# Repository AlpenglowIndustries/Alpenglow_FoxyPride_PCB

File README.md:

# Foxy_Pride_PCB
An awesome SMT soldering board with space for writing pronouns, where you can choose your own pride-themed colors for the LEDs.
The circuit uses a 555 timer to create a clock signal, which is fed into the decade counter to light the LEDs.
You can change the blink rate by swapping out the capacitor!

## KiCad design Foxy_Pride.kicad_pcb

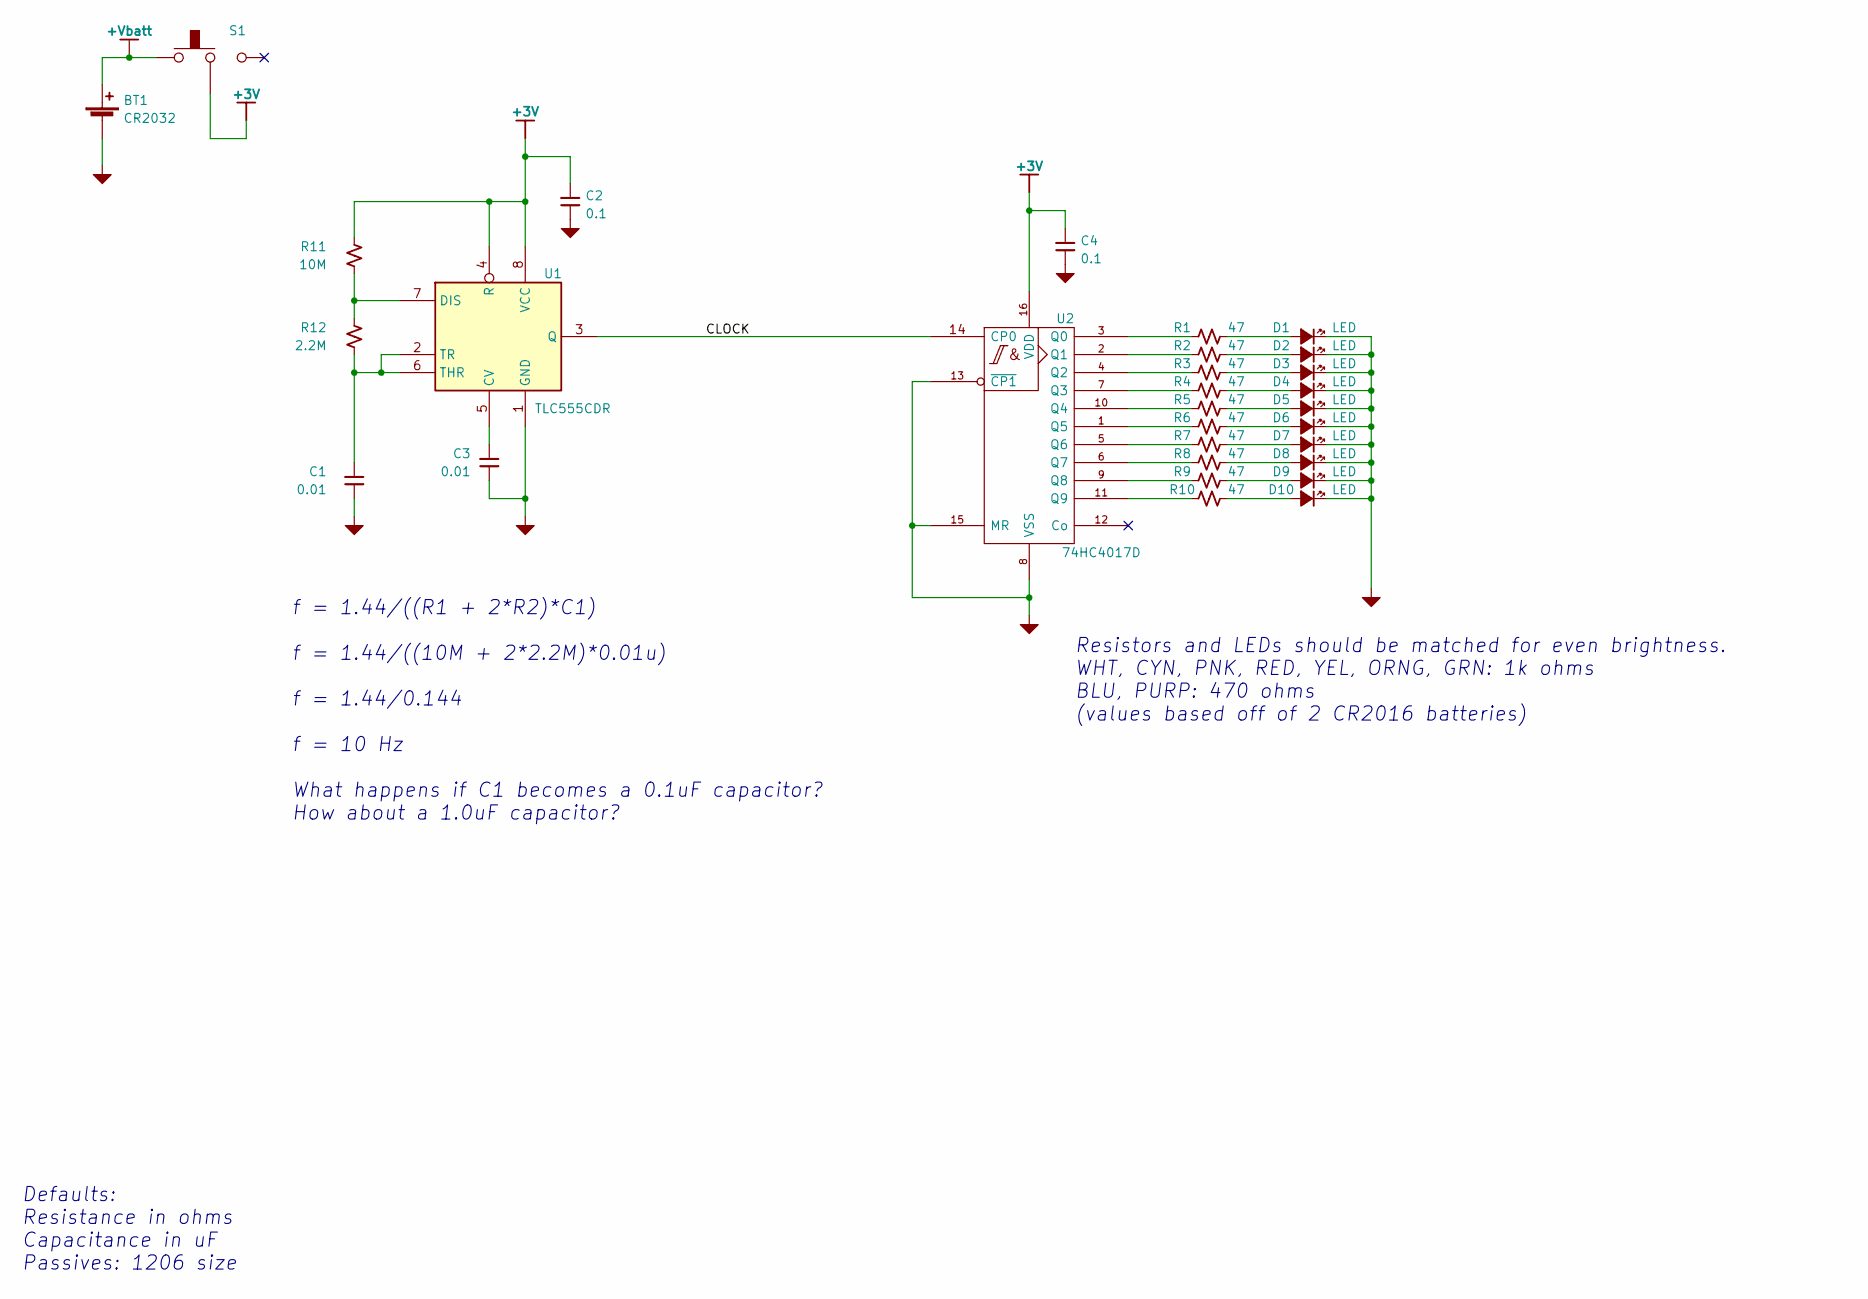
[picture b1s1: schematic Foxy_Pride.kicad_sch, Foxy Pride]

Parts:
BT1: CR2032; BatteryHolder_CR2032_SMT
C1, C3: 0.01; R_1206_3216Metric_Pad1.30x1.75mm_HandSolder
C2, C4: 0.1; R_1206_3216Metric_Pad1.30x1.75mm_HandSolder
D1, D2, D3, D4, D5, D6, D7, D8, D9, D10: LED; LED_1206+
R1, R2, R3, R4, R5, R6, R7, R8, R9, R10: 47; R_1206_3216Metric_Pad1.30x1.75mm_HandSolder
R11: 10M; R_1206_3216Metric_Pad1.30x1.75mm_HandSolder
R12: 2.2M; R_1206_3216Metric_Pad1.30x1.75mm_HandSolder
S1: SMT_Slide_Switch; SW_SPDT_SMT_RTA
U1: TLC555CDR; SO-8
U2: 74HC4017D; SO-16

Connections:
+3V: C2.1, C4.1, R11.1, S1.2, U1.4 (R), U1.8 (VCC), U2.16 (VDD)
+Vbatt: BT1.1 (+), S1.1
/CLOCK: U1.3 (Q), U2.14 (CP0)
GND: BT1.2 (-), C1.2, C2.2, C3.2, C4.2, D1.1 (K), D2.1 (K), D3.1 (K), D4.1 (K), D5.1 (K), D6.1 (K), D7.1 (K), D8.1 (K), D9.1 (K), D10.1 (K), U1.1 (GND), U2.8 (VSS), U2.13 (~CP1), U2.15 (MR)
unnamed: C1.1, R12.2, U1.2 (TR), U1.6 (THR)
unnamed: C3.1, U1.5 (CV)
unnamed: D1.2 (A), R1.1
unnamed: D2.2 (A), R2.1
unnamed: D3.2 (A), R3.1
unnamed: D4.2 (A), R4.1
unnamed: D5.2 (A), R5.1
unnamed: D6.2 (A), R6.1
unnamed: D7.2 (A), R7.1
unnamed: D8.2 (A), R8.1
unnamed: D9.2 (A), R9.1
unnamed: D10.2 (A), R10.1
unnamed: R1.2, U2.3 (Q0)
unnamed: R2.2, U2.2 (Q1)
unnamed: R3.2, U2.4 (Q2)
unnamed: R4.2, U2.7 (Q3)
unnamed: R5.2, U2.10 (Q4)
unnamed: R6.2, U2.1 (Q5)
unnamed: R7.2, U2.5 (Q6)
unnamed: R8.2, U2.6 (Q7)
unnamed: R9.2, U2.9 (Q8)
unnamed: R10.2, U2.11 (Q9)
unnamed: R11.2, R12.1, U1.7 (DIS)

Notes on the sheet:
Defaults: Resistance in ohms Capacitance in uF Passives: 1206 size
f = 1.44/((R1 + 2*R2)*C1) f = 1.44/((10M + 2*2.2M)*0.01u) f = 1.44/0.144 f = 10 Hz What happens if C1 becomes a 0.1uF capacitor? How about a 1.0uF capacitor?
Resistors and LEDs should be matched for even brightness. WHT, CYN, PNK, RED, YEL, ORNG, GRN: 1k ohms BLU, PURP: 470 ohms (values based off of 2 CR2016 batteries)

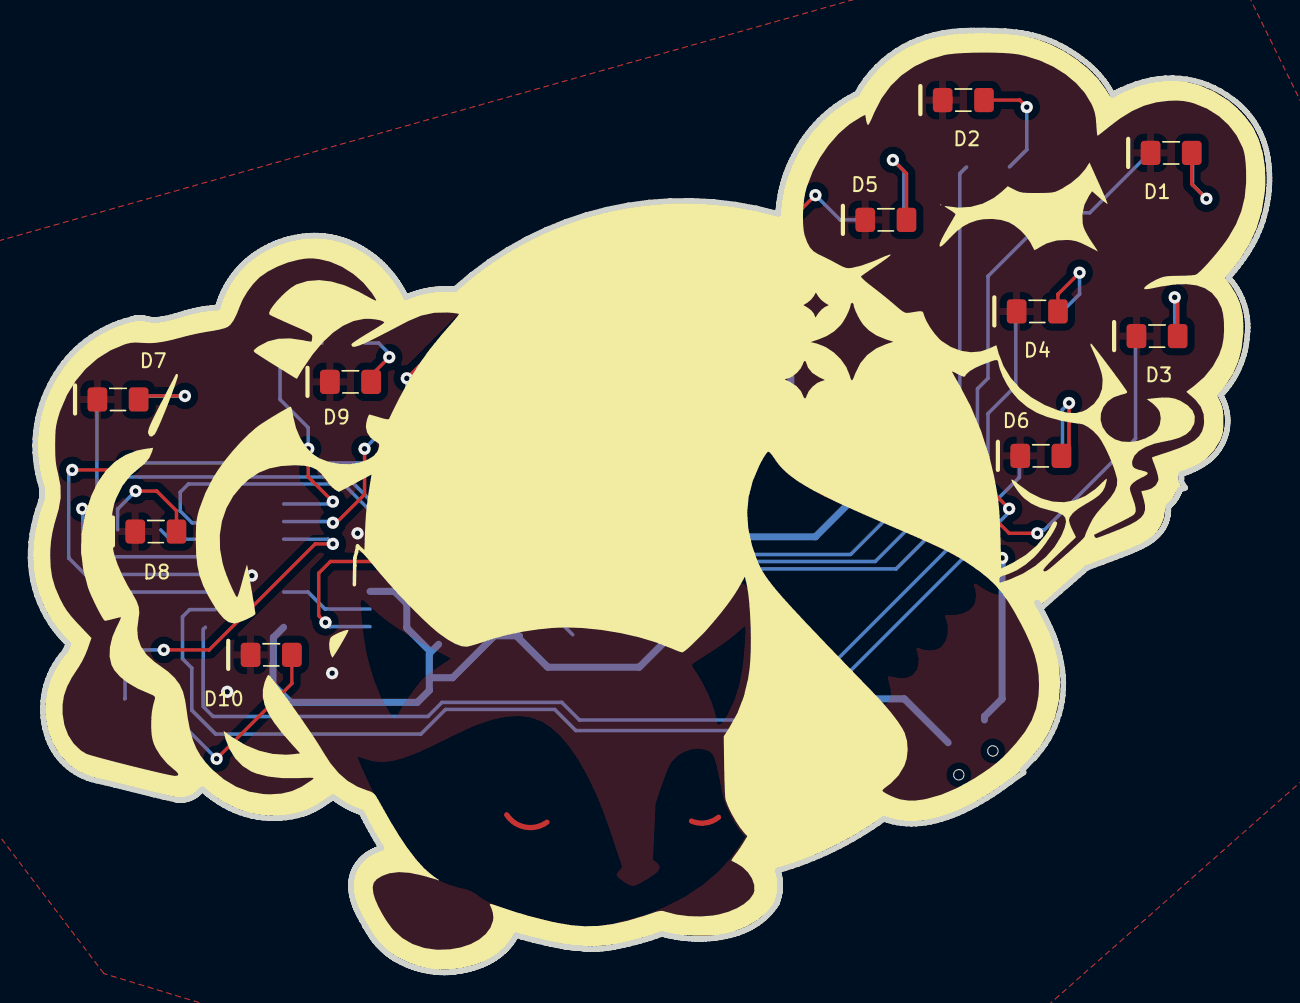
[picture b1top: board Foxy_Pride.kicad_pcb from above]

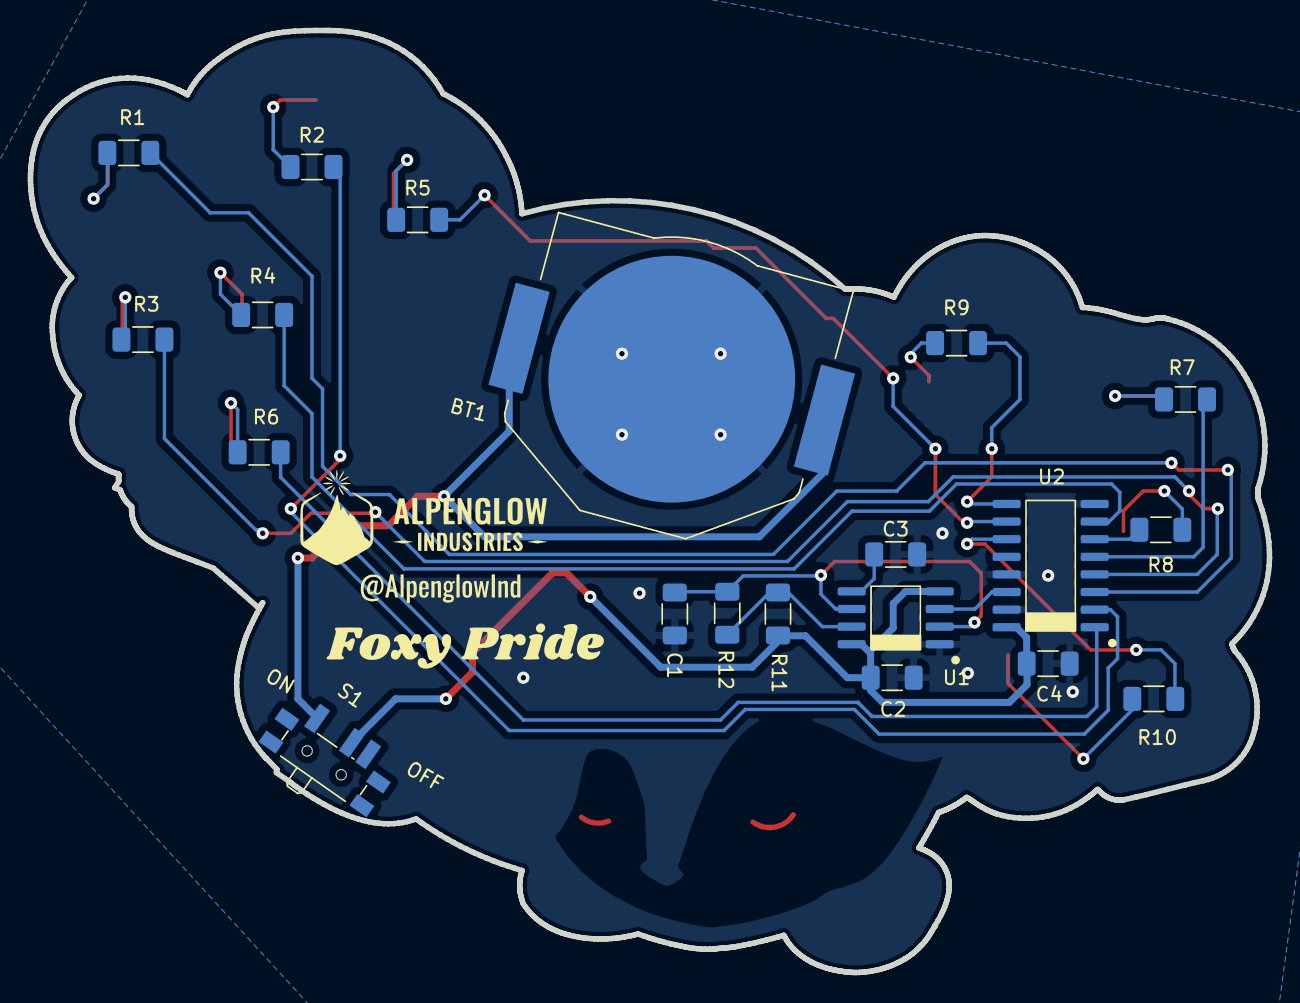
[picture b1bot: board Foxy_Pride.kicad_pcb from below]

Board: 2 copper layers, 89.3 x 67.9 mm, 30 parts (20 on the bottom side), 27 nets.

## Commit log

2022-04-26 initial commit of files
2022-04-26 removed .zip from repo
2022-04-29 PCB layout editing
2022-05-02 PCB Layout
2022-05-03 Added vias to connect GND
2022-05-03 changes to make some routing shorter, fixed switch and power, added eyes in copper
2022-05-04 Finalized design and layout on Foxy Pride PCB
2022-05-06 Deleted unused files
2022-05-17 Re annontated schematic so resistors and LEDs have matching refrence designators
2022-05-19 Changed schematic layout. Put resistor in correct spot. Update PCB.
2022-05-19 Repositioned resistor and capacitor
2022-05-23 Update 555 timer footprint and decasde counter. had to fix a couple tranes after.
2022-06-01 Updated Final Design
2022-06-03 generated gerbers for ordering
2022-09-15 Updated board name with font, updated @alpenglowind with font
2022-10-24 Generated Schematic PDF
2022-10-26 Assembly drawings, BOM, schematic
2022-10-26 Added title block, Updated schematic PDF
2022-10-27 updated BOM
2022-10-27 Updated gitignore, changed BOM to CSV file
